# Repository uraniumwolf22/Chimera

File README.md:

# Chimera
Repository for the entire Chimera project
Note: Vault is meant to be opened with obsidian

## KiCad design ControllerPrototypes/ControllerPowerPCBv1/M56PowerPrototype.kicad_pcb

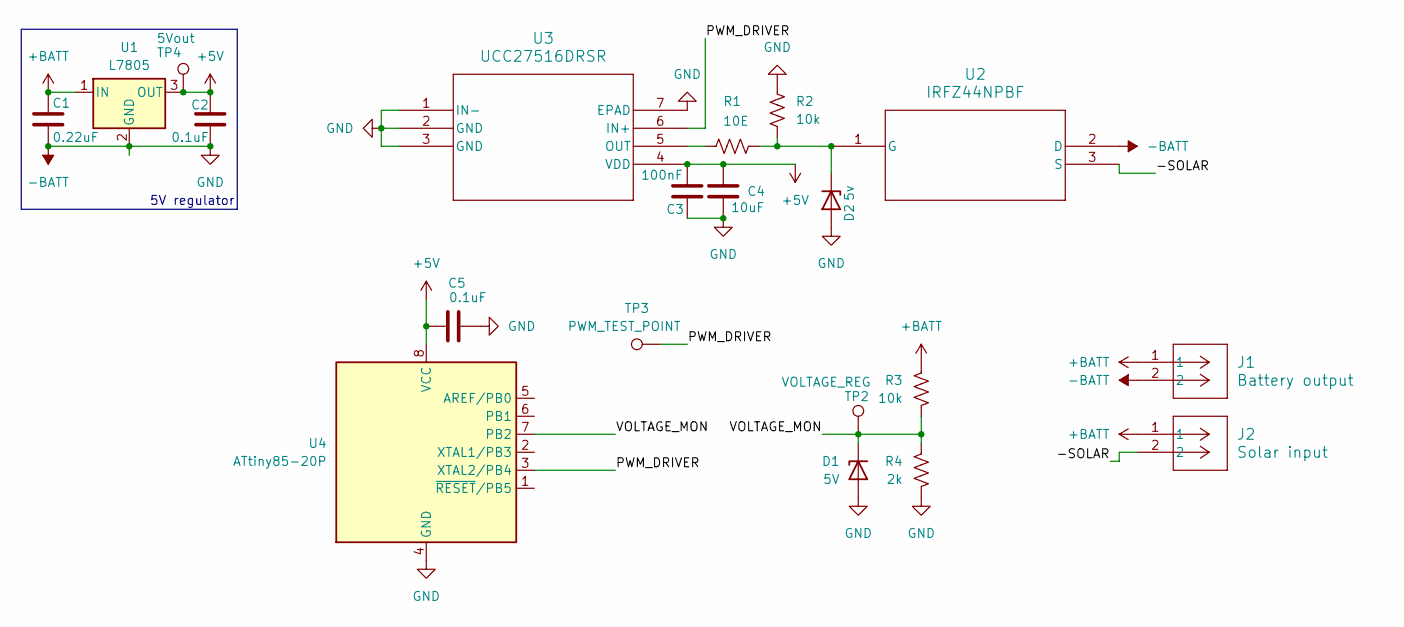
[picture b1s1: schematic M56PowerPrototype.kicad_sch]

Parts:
C1: 0.22uF; C_1206_3216Metric
C2: 0.1uF; C_1206_3216Metric
C3: 100nF; C_0603_1608Metric
C4: 10uF; C_0603_1608Metric
C5: 0.1uF; C_0805_2012Metric
D1: 5V; D_DO-35_SOD27_P7.62mm_Horizontal
D2: 5v; D_DO-35_SOD27_P7.62mm_Horizontal
J1: Battery output; CONN_4DB-P108-02_TEC
J2: Solar input; CONN_4DB-P108-02_TEC
R1: 10E; R_0805_2012Metric
R2, R3: 10k; R_0805_2012Metric
R4: 2k; R_0805_2012Metric
TP2: VOLTAGE_REG; PinSocket_1x01_P2.54mm_Vertical
TP3: PWM_TEST_POINT; PinSocket_1x01_P2.54mm_Vertical
TP4: 5Vout; PinSocket_1x01_P2.54mm_Vertical
U1: L7805; TO-263-3_TabPin2
U2: IRFZ44NPBF; PG-TO220-3_INF
U3: UCC27516DRSR; UCC27516
U4: ATtiny85-20P; SOIC-8W_5.3x5.3mm_P1.27mm

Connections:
+5V: C2.1, C3.1, C4.1, C5.1, TP4.1, U1.3 (OUT), U3.4 (VDD), U4.8 (VCC)
+BATT: C1.2, J1.1, J2.1, R3.1, U1.1 (IN)
-BATT: C1.1, C2.2, C3.2, C4.2, C5.2, D1.2 (A), D2.2 (A), J1.2, R2.1, R4.2, U1.2 (GND), U2.2 (D), U3.1 (IN-), U3.2 (GND), U3.3 (GND), U3.7 (EPAD), U4.4 (GND)
/-SOLAR: J2.2, U2.3 (S)
/PWM_DRIVER: TP3.1, U3.6 (IN+), U4.3 (XTAL2/PB4)
/VOLTAGE_MON: D1.1 (K), R3.2, R4.1, TP2.1, U4.7 (PB2)
unnamed: D2.1 (K), R1.2, R2.2, U2.1 (G)
unnamed: R1.1, U3.5 (OUT)

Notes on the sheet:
5V regulator

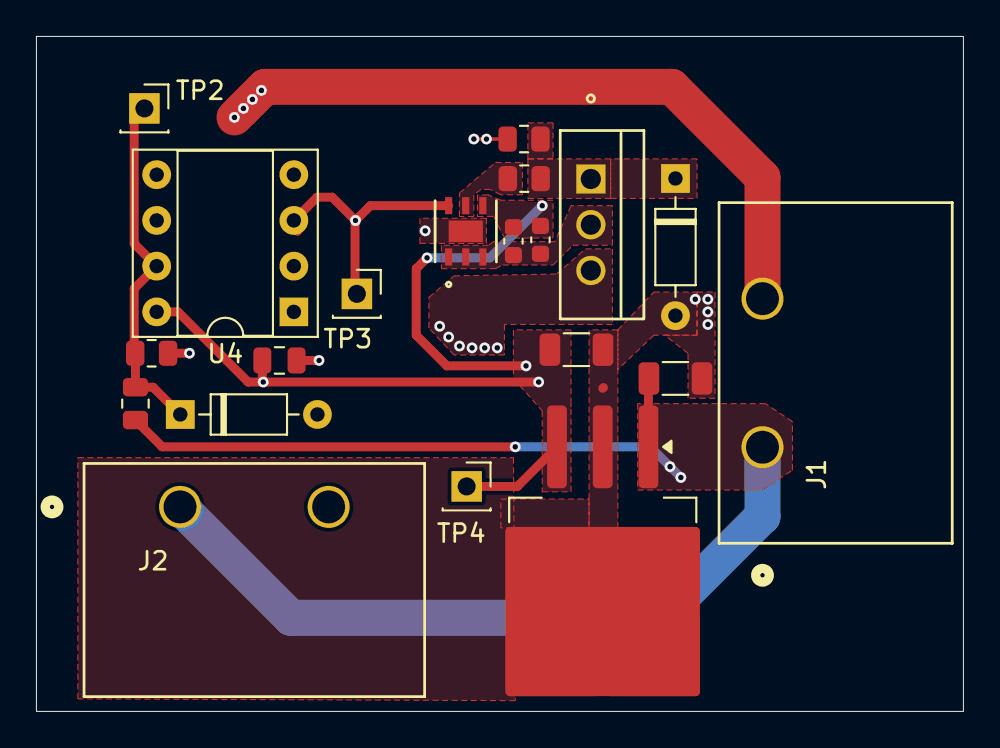
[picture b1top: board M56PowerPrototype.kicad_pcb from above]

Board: 2 copper layers, 51.5 x 37.5 mm, 20 parts (0 on the bottom side), 8 nets.

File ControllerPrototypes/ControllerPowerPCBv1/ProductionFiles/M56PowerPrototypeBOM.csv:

Designator,Comment,Footprint,DNP
C2,0.1uF,Capacitor_SMD:C_1206_3216Metric,
C5,0.1uF,Capacitor_SMD:C_0805_2012Metric,
C3,100nF,Capacitor_SMD:C_0603_1608Metric,
C1,0.22uF,Capacitor_SMD:C_1206_3216Metric,
C4,10uF,Capacitor_SMD:C_0603_1608Metric,
R1,10E,Resistor_SMD:R_0805_2012Metric,
R4,2k,Resistor_SMD:R_0805_2012Metric,
R2,10k,Resistor_SMD:R_0805_2012Metric,
R3,10k,Resistor_SMD:R_0805_2012Metric,
U1,L7805,Package_TO_SOT_SMD:TO-263-3_TabPin2,
U3,UCC27516DRSR,UCC27516:UCC27516,

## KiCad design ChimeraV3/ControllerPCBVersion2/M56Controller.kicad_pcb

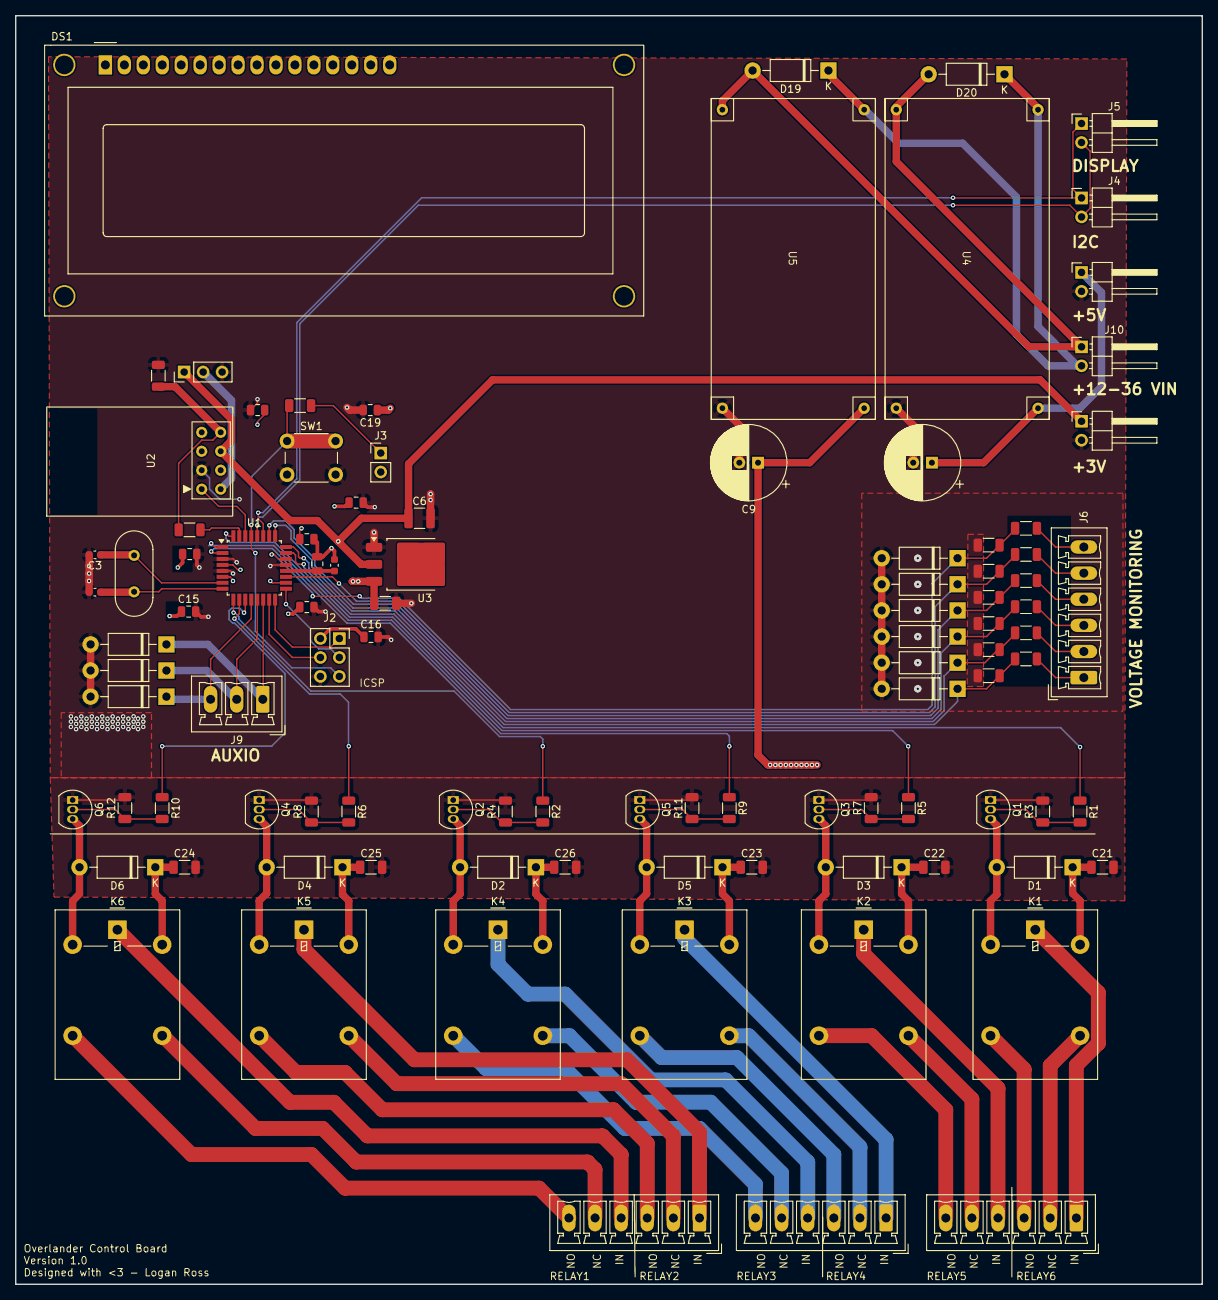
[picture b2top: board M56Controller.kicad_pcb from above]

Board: 4 copper layers, 159.0 x 170.0 mm, 99 parts (0 on the bottom side), 71 nets.

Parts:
C1: 100nf; C_0805_2012Metric
C2: 1nf; C_0603_1608Metric
C3, C4: 22pf; C_0603_1608Metric
C5, C21, C22, C23, C24, C25, C26: 10uf; C_1206_3216Metric
C6: 100uf; C_1210_3225Metric
C9, C11: 470uf; CP_Radial_D10.0mm_P2.50mm
C13, C14, C15, C20: 1uf; C_0805_2012Metric
C16, C17, C18, C19: 0.1uf; C_0805_2012Metric
D1, D2, D3, D4, D5, D6, D19, D20: D; D_DO-41_SOD81_P10.16mm_Horizontal
D7, D8, D9, D10, D11, D12, D16, D17, D18: 5.1v; D_DO-41_SOD81_P10.16mm_Horizontal
DS1: WC1602A
J1: ResetJumper; PinHeader_1x03_P2.54mm_Vertical
J2: AVR-ISP-6; PinSocket_2x03_P2.54mm_Vertical
J3: RESET_DISABLE; PinHeader_1x02_P2.54mm_Vertical
J4: I2C_AUX; PinHeader_1x02_P2.54mm_Horizontal
J5: I2C_DISPLAY; PinHeader_1x02_P2.54mm_Horizontal
J6: VOLTAGE_MON_INPUTS; PhoenixContact_MCV_1,5_6-G-3.5_1x06_P3.50mm_Vertical
J7, J8, J14: Screw_Terminal_01x06; PhoenixContact_MCV_1,5_6-G-3.5_1x06_P3.50mm_Vertical
J9: AUXIO; PhoenixContact_MCV_1,5_3-G-3.5_1x03_P3.50mm_Vertical
J10: 12-36v; PinHeader_1x02_P2.54mm_Horizontal
J12: 5VOUT; PinHeader_1x02_P2.54mm_Horizontal
J13: 3.3VOUT; PinHeader_1x02_P2.54mm_Horizontal
K1, K2, K3, K4, K5, K6: G5LE-1; Relay_SPDT_Omron-G5LE-1
Q1, Q2, Q3, Q4, Q5, Q6: 2N3904; TO-92_Inline
R1, R2, R5, R6, R9, R10: 1k; R_1206_3216Metric
R3, R4, R7, R8, R11, R12: 15k; R_1206_3216Metric
R13: 20k; R_1206_3216Metric
R14: 10k; R_1206_3216Metric
R15: 10K; R_1206_3216Metric
R16, R18, R20, R22, R24, R26: 100k; R_1206_3216Metric
R17, R19, R21, R23, R25, R27: 16k; R_1206_3216Metric
SW1: SW_RESET; SW_PUSH_6mm_H8mm
U1: ATmega328-A; TQFP-32_7x7mm_P0.8mm
U2: ESP-01v090; ESP-01
U3: LM1117MP-3.3; TO-252-3_TabPin2
U4, U5: AmazonBuckConverter
Y1: 16Mhz; Crystal_HC49-4H_Vertical

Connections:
+3.3V: C6.1, J1.1, J13.1, U2.7 (VCC), U3.2 (VO)
+5V: C5.1, C11.1, C13.1, C14.1, C15.1, C16.1, C17.1, C18.1, C19.1, C20.1, J2.2 (VCC), J3.2, J12.1, U1.4 (VCC), U1.6 (VCC), U1.18 (AVCC), U3.3 (VI), U4.3 (Vout+)
+12V: C9.1, C21.1, C22.1, C23.1, C24.1, C25.1, C26.1, D1.1 (K), D2.1 (K), D3.1 (K), D4.1 (K), D5.1 (K), D6.1 (K), K1.5, K2.5, K3.5, K4.5, K5.5, K6.5, U5.3 (Vout+)
/Controller/ANALOG6: D11.1 (K), R24.2, R25.1, U1.19 (ADC6)
/Controller/ANALOG7: D12.1 (K), R26.2, R27.1, U1.22 (ADC7)
/Controller/AUXIO1: D16.1 (K), J9.3, U1.12 (PB0)
/Controller/AUXIO2: D17.1 (K), J9.2, U1.13 (PB1)
/Controller/AUXIO3: D18.1 (K), J9.1, U1.14 (PB2)
/Controller/ESP_RST: J1.2, U2.5 (RST)
/Controller/ESP_RX: R14.2, U1.31 (PD1)
/Controller/ESP_TX: U1.30 (PD0), U2.1 (UTXD)
/Controller/MCU_MISO: J2.1 (MISO), U1.16 (PB4)
/Controller/MCU_MOSI: J2.4 (MOSI), U1.15 (PB3)
/Controller/MCU_RESET: J2.5 (~RST), R15.1, SW1.1, U1.29 (~RESET/PC6)
/Controller/MCU_SCK: J2.3 (SCK), U1.17 (PB5)
/Controller/MCU_SCL: J4.2, J5.2, U1.28 (PC5)
/Controller/MCU_SDA: J4.1, J5.1, U1.27 (PC4)
/Controller/RELAY1: R1.1, U1.32 (PD2)
/Controller/RELAY2: R5.1, U1.1 (PD3)
/Controller/RELAY3: R9.1, U1.2 (PD4)
/Controller/RELAY4: R2.1, U1.9 (PD5)
/Controller/RELAY5: R6.1, U1.10 (PD6)
/Controller/RELAY6: R10.1, U1.11 (PD7)
/Controller/VoltageDividers/AVIN1: J6.1, R16.1
/Controller/VoltageDividers/AVIN2: J6.2, R18.1
/Controller/VoltageDividers/AVIN3: J6.3, R20.1
/Controller/VoltageDividers/AVIN4: J6.4, R22.1
/Controller/VoltageDividers/AVIN5: J6.5, R24.1
/Controller/VoltageDividers/AVIN6: J6.6, R26.1
/Controller/VoltageDividers/AVOUT1: D7.1 (K), R16.2, R17.1, U1.23 (PC0)
/Controller/VoltageDividers/AVOUT2: D8.1 (K), R18.2, R19.1, U1.24 (PC1)
/Controller/VoltageDividers/AVOUT3: D9.1 (K), R20.2, R21.1, U1.25 (PC2)
/Controller/VoltageDividers/AVOUT4: D10.1 (K), R22.2, R23.1, U1.26 (PC3)
/Power Supply/VIN: D19.1 (K), D20.1 (K), J10.2, U4.1 (V+), U5.1 (V+)
/RelayDriver/RELAY1IN: J7.1, K1.1
/RelayDriver/RELAY1OUT_NC: J7.2, K1.4
/RelayDriver/RELAY1OUT_NO: J7.3, K1.3
/RelayDriver/RELAY2IN: J7.4, K2.1
/RelayDriver/RELAY2OUT_NC: J7.5, K2.4
/RelayDriver/RELAY2OUT_NO: J7.6, K2.3
/RelayDriver/RELAY3IN: J8.1, K3.1
/RelayDriver/RELAY3OUT_NC: J8.2, K3.4
/RelayDriver/RELAY3OUT_NO: J8.3, K3.3
/RelayDriver/RELAY4IN: J8.4, K4.1
/RelayDriver/RELAY4OUT_NC: J8.5, K4.4
/RelayDriver/RELAY4OUT_NO: J8.6, K4.3
/RelayDriver/RELAY5IN: J14.1, K5.1
/RelayDriver/RELAY5OUT_NC: J14.2, K5.4
/RelayDriver/RELAY5OUT_NO: J14.3, K5.3
/RelayDriver/RELAY6IN: J14.4, K6.1
/RelayDriver/RELAY6OUT_NC: J14.5, K6.4
/RelayDriver/RELAY6OUT_NO: J14.6, K6.3
GND: C1.1, C2.1, C3.2, C4.2, C5.2, C6.2, C9.2, C11.2, C13.2, C14.2, C15.2, C16.2, C17.2, C18.2, C19.2, C20.2, C21.2, C22.2, C23.2, C24.2, C25.2, C26.2, D7.2 (A), D8.2 (A), D9.2 (A), D10.2 (A), D11.2 (A), D12.2 (A), D16.2 (A), D17.2 (A), D18.2 (A), J1.3, J2.6 (GND), J12.2, J13.2, Q1.1 (E), Q2.1 (E), Q3.1 (E), Q4.1 (E), Q5.1 (E), Q6.1 (E), R3.2, R4.2, R7.2, R8.2, R11.2, R12.2, R13.2, R17.2, R19.2, R21.2, R23.2, R25.2, R27.2, SW1.2, U1.3 (GND), U1.5 (GND), U1.21 (GND), U2.2 (GND), U3.1 (GND), U4.4 (Vout-), U5.4 (Vout-)
unnamed: D1.2 (A), K1.2, Q1.3 (C)
unnamed: D2.2 (A), K4.2, Q2.3 (C)
unnamed: D3.2 (A), K2.2, Q3.3 (C)
unnamed: D4.2 (A), K5.2, Q4.3 (C)
unnamed: D5.2 (A), K3.2, Q5.3 (C)
unnamed: D6.2 (A), K6.2, Q6.3 (C)
unnamed: D19.2 (A), D20.2 (A), J10.1, U4.2 (V-), U5.2 (V-)
unnamed: J3.1, R15.2
unnamed: Q1.2 (B), R1.2, R3.1
unnamed: Q2.2 (B), R2.2, R4.1
unnamed: Q3.2 (B), R5.2, R7.1
unnamed: Q4.2 (B), R6.2, R8.1
unnamed: Q5.2 (B), R9.2, R11.1
unnamed: Q6.2 (B), R10.2, R12.1
unnamed: C1.2, C2.2, U1.20 (AREF)
unnamed: C3.1, U1.7 (XTAL1/PB6), Y1.2
unnamed: C4.1, U1.8 (XTAL2/PB7), Y1.1
unnamed: R13.1, R14.1, U2.8 (URXD)

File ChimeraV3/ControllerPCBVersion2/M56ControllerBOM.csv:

"Reference","Value","Datasheet","Footprint","Qty","DNP"
"C1","100nf","~","Capacitor_SMD:C_0805_2012Metric","1",""
"C2","1nf","~","Capacitor_SMD:C_0603_1608Metric","1",""
"C3,C4","22pf","~","Capacitor_SMD:C_0603_1608Metric","2",""
"C5,C21,C22,C23,C24,C25,C26","10uf","~","Capacitor_SMD:C_1206_3216Metric","7",""
"C6","100uf","~","Capacitor_SMD:C_1210_3225Metric","1",""
"C9,C11","470uf","~","Capacitor_THT:CP_Radial_D10.0mm_P2.50mm","2",""
"C13,C14,C15,C20","1uf","~","Capacitor_SMD:C_0805_2012Metric","4",""
"C16,C17,C18,C19","0.1uf","~","Capacitor_SMD:C_0805_2012Metric","4",""
"D1,D2,D3,D4,D5,D6,D19,D20","D","~","Diode_THT:D_DO-41_SOD81_P10.16mm_Horizontal","8",""
"D7,D8,D9,D10,D11,D12,D16,D17,D18","5.1v","~","Diode_THT:D_DO-41_SOD81_P10.16mm_Horizontal","9",""
"DS1","WC1602A","http://www.wincomlcd.com/pdf/WC1602A-SFYLYHTC06.pdf","Display:WC1602A","1",""
"J1","ResetJumper","~","Connector_PinHeader_2.54mm:PinHeader_1x03_P2.54mm_Vertical","1",""
"J2","AVR-ISP-6","~","Connector_PinSocket_2.54mm:PinSocket_2x03_P2.54mm_Vertical","1",""
"J3","RESET_DISABLE","~","Connector_PinHeader_2.54mm:PinHeader_1x02_P2.54mm_Vertical","1",""
"J4","I2C_AUX","~","Connector_PinHeader_2.54mm:PinHeader_1x02_P2.54mm_Horizontal","1",""
"J5","I2C_DISPLAY","~","Connector_PinHeader_2.54mm:PinHeader_1x02_P2.54mm_Horizontal","1",""
"J6","VOLTAGE_MON_INPUTS","~","Connector_Phoenix_MC:PhoenixContact_MCV_1,5_6-G-3.5_1x06_P3.50mm_Vertical","1",""
"J7,J8,J14","Screw_Terminal_01x06","~","Connector_Phoenix_MC:PhoenixContact_MCV_1,5_6-G-3.5_1x06_P3.50mm_Vertical","3",""
"J9","AUXIO","~","Connector_Phoenix_MC:PhoenixContact_MCV_1,5_3-G-3.5_1x03_P3.50mm_Vertical","1",""
"J10","12-36v","~","Connector_PinHeader_2.54mm:PinHeader_1x02_P2.54mm_Horizontal","1",""
"J12","5VOUT","~","Connector_PinHeader_2.54mm:PinHeader_1x02_P2.54mm_Horizontal","1",""
"J13","3.3VOUT","~","Connector_PinHeader_2.54mm:PinHeader_1x02_P2.54mm_Horizontal","1",""
"K1,K2,K3,K4,K5,K6","G5LE-1","http://www.omron.com/ecb/products/pdf/en-g5le.pdf","Relay_THT:Relay_SPDT_Omron-G5LE-1","6",""
"Q1,Q2,Q3,Q4,Q5,Q6","2N3904","https://www.onsemi.com/pub/Collateral/2N3903-D.PDF","Package_TO_SOT_THT:TO-92_Inline","6",""
"R1,R2,R5,R6,R9,R10","1k","~","Resistor_SMD:R_1206_3216Metric","6",""
"R3,R4,R7,R8,R11,R12","15k","~","Resistor_SMD:R_1206_3216Metric","6",""
"R13","20k","~","Resistor_SMD:R_1206_3216Metric","1",""
"R14","10k","~","Resistor_SMD:R_1206_3216Metric","1",""
"R15","10K","~","Resistor_SMD:R_1206_3216Metric","1",""
"R16,R18,R20,R22,R24,R26","100k","~","Resistor_SMD:R_1206_3216Metric","6",""
"R17,R19,R21,R23,R25,R27","16k","~","Resistor_SMD:R_1206_3216Metric","6",""
"SW1","SW_RESET","~","Button_Switch_THT:SW_PUSH_6mm_H8mm","1",""
"U1","ATmega328-A","http://ww1.microchip.com/downloads/en/DeviceDoc/ATmega328_P%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","Package_QFP:TQFP-32_7x7mm_P0.8mm","1",""
"U2","ESP-01v090","http://l0l.org.uk/2014/12/esp8266-modules-hardware-guide-got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","RF_Module:ESP-01","1",""
"U3","LM1117MP-3.3","http://www.ti.com/lit/ds/symlink/lm1117.pdf","Package_TO_SOT_SMD:TO-252-3_TabPin2","1",""
"U4,U5","~","","AmazonPowerSupply:AmazonBuckConverter","2",""
"Y1","16Mhz","~","Crystal:Crystal_HC49-4H_Vertical","1",""

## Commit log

2025-07-24 Some cleanup
2025-07-24 Added logic simulation
